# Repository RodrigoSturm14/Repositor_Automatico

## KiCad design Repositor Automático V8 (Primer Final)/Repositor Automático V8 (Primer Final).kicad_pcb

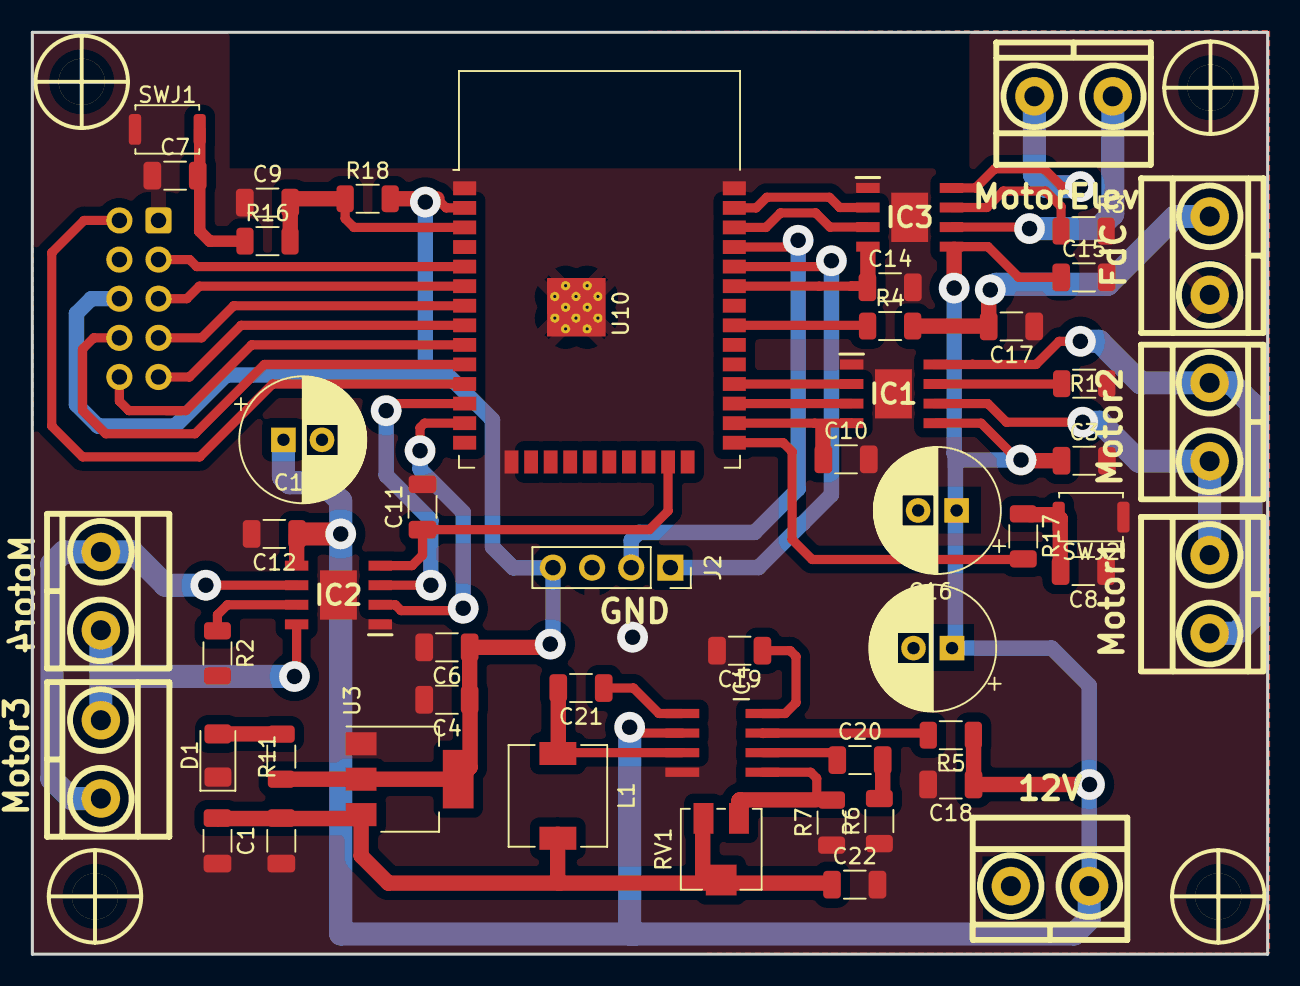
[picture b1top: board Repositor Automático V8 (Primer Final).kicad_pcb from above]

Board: 2 copper layers, 80.2 x 59.8 mm, 57 parts (1 on the bottom side), 45 nets.

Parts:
12V: Alimentacion 12V; BORNERA2_AZUL
C1, C6: 10u; C_1206_3216Metric
C2, C3, C4, C7, C8, C9, C10, C11, C12, C14, C15, C17, C19: 0.1u; C_1206_3216Metric
C5, C13, C16: 100u; CP_Radial_D8.0mm_P2.50mm
C18, C22: 12u; C_1206_3216Metric
C20: 4.8n; C_1206_3216Metric
C21: 10n; C_1206_3216Metric
D1: LED; LED_1206_3216Metric
IC1, IC2, IC3: TB67H450AFNG,EL; SOIC127P600X170-9N
IC4: MP2307; SO8-TH
J2: UART; PinSocket_1x04_P2.54mm_Vertical
J3: Motor2; BORNERA2_AZUL
J4: Motor1; BORNERA2_AZUL
J5: Motor3; BORNERA2_AZUL
J6: Motor4; BORNERA2_AZUL
J7: MotorElev; BORNERA2_AZUL
J8: Screw_Terminal_01x10; IDC-Header_2x05_P2.54mm_Horizontal
J11: FdC; BORNERA2_AZUL
L1: 2u; L_6.3x6.3_H3
R1, R2, R3: 0.22; R_1206_3216Metric
R4, R5, R16, R17: 100k; R_1206_3216Metric
R6, R7: 8.2k; R_1206_3216Metric
R11: 5.1k; R_1206_3216Metric
R18: 10k; R_1206_3216Metric
RV1: 220k; Potentiometer_Vishay_TS53YJ_Vertical
SWJ1, SWJ2: SW_MEC_5G; SW_Push_SPST_NO_Alps_SKRK
U3: AMS1117-3.3; SOT-223-3_TabPin2
U10: ESP32-WROOM-32; ESP32-WROOM-32D
hole_3mm, hole_3mm#2, hole_3mm#3, hole_3mm#4: VAL**; hole_3mm

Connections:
/3V3: C4.1, C6.1, J2.4, J8.6, R11.1, R18.2, U3.2 (VO), U10.2 (VDD)
/5V: C1.1, C2.1, C22.1, L1.2, RV1.1, RV1.2, U3.3 (VI)
/BOOT: R17.2, U10.25 (IO0)
/EN: C9.2, R16.2, R18.1, U10.3 (EN)
/EN Elev: C14.1, IC3.4 (VREF), U10.33 (IO21)
/EnA: C10.1, IC1.4 (VREF), U10.26 (IO4)
/EnB: C11.1, IC2.4 (VREF), U10.23 (IO15)
/FC: R4.1, U10.31 (IO19)
/IN1: IC1.3 (IN1), U10.27 (IO16)
/IN2: IC1.2 (IN2), U10.28 (IO17)
/IN3: IC2.2 (IN2), U10.13 (IO14)
/IN4: IC2.3 (IN1), U10.12 (IO27)
/IN5: IC3.2 (IN2), U10.37 (IO23)
/IN6: IC3.3 (IN1), U10.36 (IO22)
/RXD0: J2.1, U10.34 (RXD0/IO3)
/Sen1: J8.8, U10.10 (IO25)
/Sen2: J8.10, U10.9 (IO33)
/Sen3: J8.9, U10.8 (IO32)
/Sen4: J8.7, U10.7 (IO35)
/Sen5: J8.5, U10.6 (IO34)
/Sen6: J8.3, U10.5 (SENSOR_VN)
/Sen7: J8.2, U10.11 (IO26)
/TXD0: J2.2, U10.35 (TXD0/IO1)
/Vin: 12V.1, C3.1, C5.1, C12.1, C13.1, C15.1, C16.1, C18.1, IC1.5 (VM), IC2.5 (VM), IC3.5 (VM), IC4.2 (IN), R5.1
GND: 12V.2, C1.2, C2.2, C3.2, C4.2, C5.2, C6.2, C7.1, C8.1, C9.1, C10.2, C11.2, C12.2, C13.2, C14.2, C15.2, C16.2, C17.1, C18.2, C19.2, C22.2, D1.1 (K), IC1.1 (GND), IC1.9 (EP), IC2.1 (GND), IC2.9 (EP), IC3.1 (GND), IC3.9 (EP), IC4.4 (GND), J2.3, J8.1, J11.2, R1.2, R2.2, R3.2, R6.1, R7.1, SWJ1.1 (A), SWJ2.1 (A), U3.1 (GND), U10.1 (GND), U10.15 (GND), U10.38 (GND), U10.39 (GND)
unnamed: C20.2, R6.2
unnamed: D1.2 (A), R11.2
unnamed: IC1.6 (OUT1), J3.1, J4.1
unnamed: IC1.8 (OUT2), J3.2, J4.2
unnamed: IC1.7 (RS), R1.1
unnamed: IC2.6 (OUT1), J5.1, J6.1
unnamed: IC2.8 (OUT2), J5.2, J6.2
unnamed: IC2.7 (RS), R2.1
unnamed: IC3.6 (OUT1), J7.1
unnamed: IC3.8 (OUT2), J7.2
unnamed: IC3.7 (RS), R3.1
unnamed: C21.1, IC4.1 (BS)
unnamed: C20.1, IC4.6 (COMP)
unnamed: IC4.7 (EN), R5.2
unnamed: IC4.5 (FB), R7.2, RV1.3
unnamed: C19.1, IC4.8 (SS)
unnamed: C21.2, IC4.3 (SW), L1.1
unnamed: C17.2, J11.1, R4.2
unnamed: C7.2, R16.1, SWJ1.2 (B)
unnamed: C8.2, R17.1, SWJ2.2 (B)

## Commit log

2023-08-04 Subido
2023-09-12 Agregue carpeta sistema embebido code
2023-09-14 Delete Repocitor autmático directory
    Limpieza de archivos no relevantes
2023-09-14 Delete Repositor Automático V8 (Primer Final) directory
    Limpieza para organización de repositorio
2023-09-14 Delete Repositor Automático V8 (Primer Final) directory
    Limpieza y organización de repositorio
2023-09-25 Movi codigos a Software
2023-09-25 Agregue codigo HTML rodri
